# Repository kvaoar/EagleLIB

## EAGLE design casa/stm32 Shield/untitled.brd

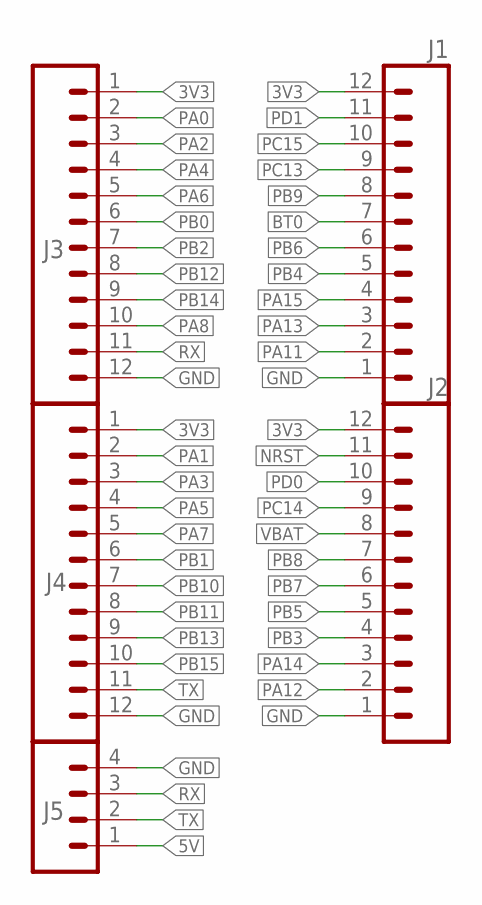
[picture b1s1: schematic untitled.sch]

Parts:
J1, J2, J3, J4: M12PTH; 1X12
J5: M04PTH; 1X04

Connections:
3V3: J1.12, J2.12, J3.1, J4.1
5V: J5.1
BT0: J1.7
GND: J1.1, J2.1, J3.12, J4.12, J5.4
NRST: J2.11
PA0: J3.2
PA1: J4.2
PA2: J3.3
PA3: J4.3
PA4: J3.4
PA5: J4.4
PA6: J3.5
PA7: J4.5
PA8: J3.10
PA11: J1.2
PA12: J2.2
PA13: J1.3
PA14: J2.3
PA15: J1.4
PB0: J3.6
PB1: J4.6
PB2: J3.7
PB3: J2.4
PB4: J1.5
PB5: J2.5
PB6: J1.6
PB7: J2.6
PB8: J2.7
PB9: J1.8
PB10: J4.7
PB11: J4.8
PB12: J3.8
PB13: J4.9
PB14: J3.9
PB15: J4.10
PC13: J1.9
PC14: J2.9
PC15: J1.10
PD0: J2.10
PD1: J1.11
RX: J3.11, J5.3
TX: J4.11, J5.2
VBAT: J2.8

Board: 2 copper layers, 5 parts (0 on the bottom side), 4 nets, no tracks yet.

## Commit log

2017-07-14 Библиотеки EagleCAD8
2017-08-15 fpga
2017-08-26 rm frame
2017-08-26 upd pin distance tqfp54 to btl
2017-08-26 removetmp
2017-09-01 add zero resistor remap Z0603/0805/1206
2017-11-11 ignore

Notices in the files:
parts and their libraries:
SparkFun-Connectors: Licensing: Creative Commons ShareAlike 4.0 International - https://creativecommons.org/licenses/by-sa/4.0
